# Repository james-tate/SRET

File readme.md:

NOT READY!!!!
Development is in progress. 

An easy to use --open hardware/software-- hardware reverse engineering tool developed using a NXP LPC4330
http://www.nxp.com/products/microcontrollers-and-processors/arm-processors/lpc-mcus/lpc4300-cortex-m4-m0:MC_1403790133078

List of tools that will be implemented:
	flash reader
	jtag
	module interface -- eg(USB->SPI; UART->I2C; etc)
	bus analyzer
	more

NOTES
Do this:
https://launchpad.net/~team-gcc-arm-embedded/+archive/ubuntu/ppa
git submodule init
then make libopencm3
then make

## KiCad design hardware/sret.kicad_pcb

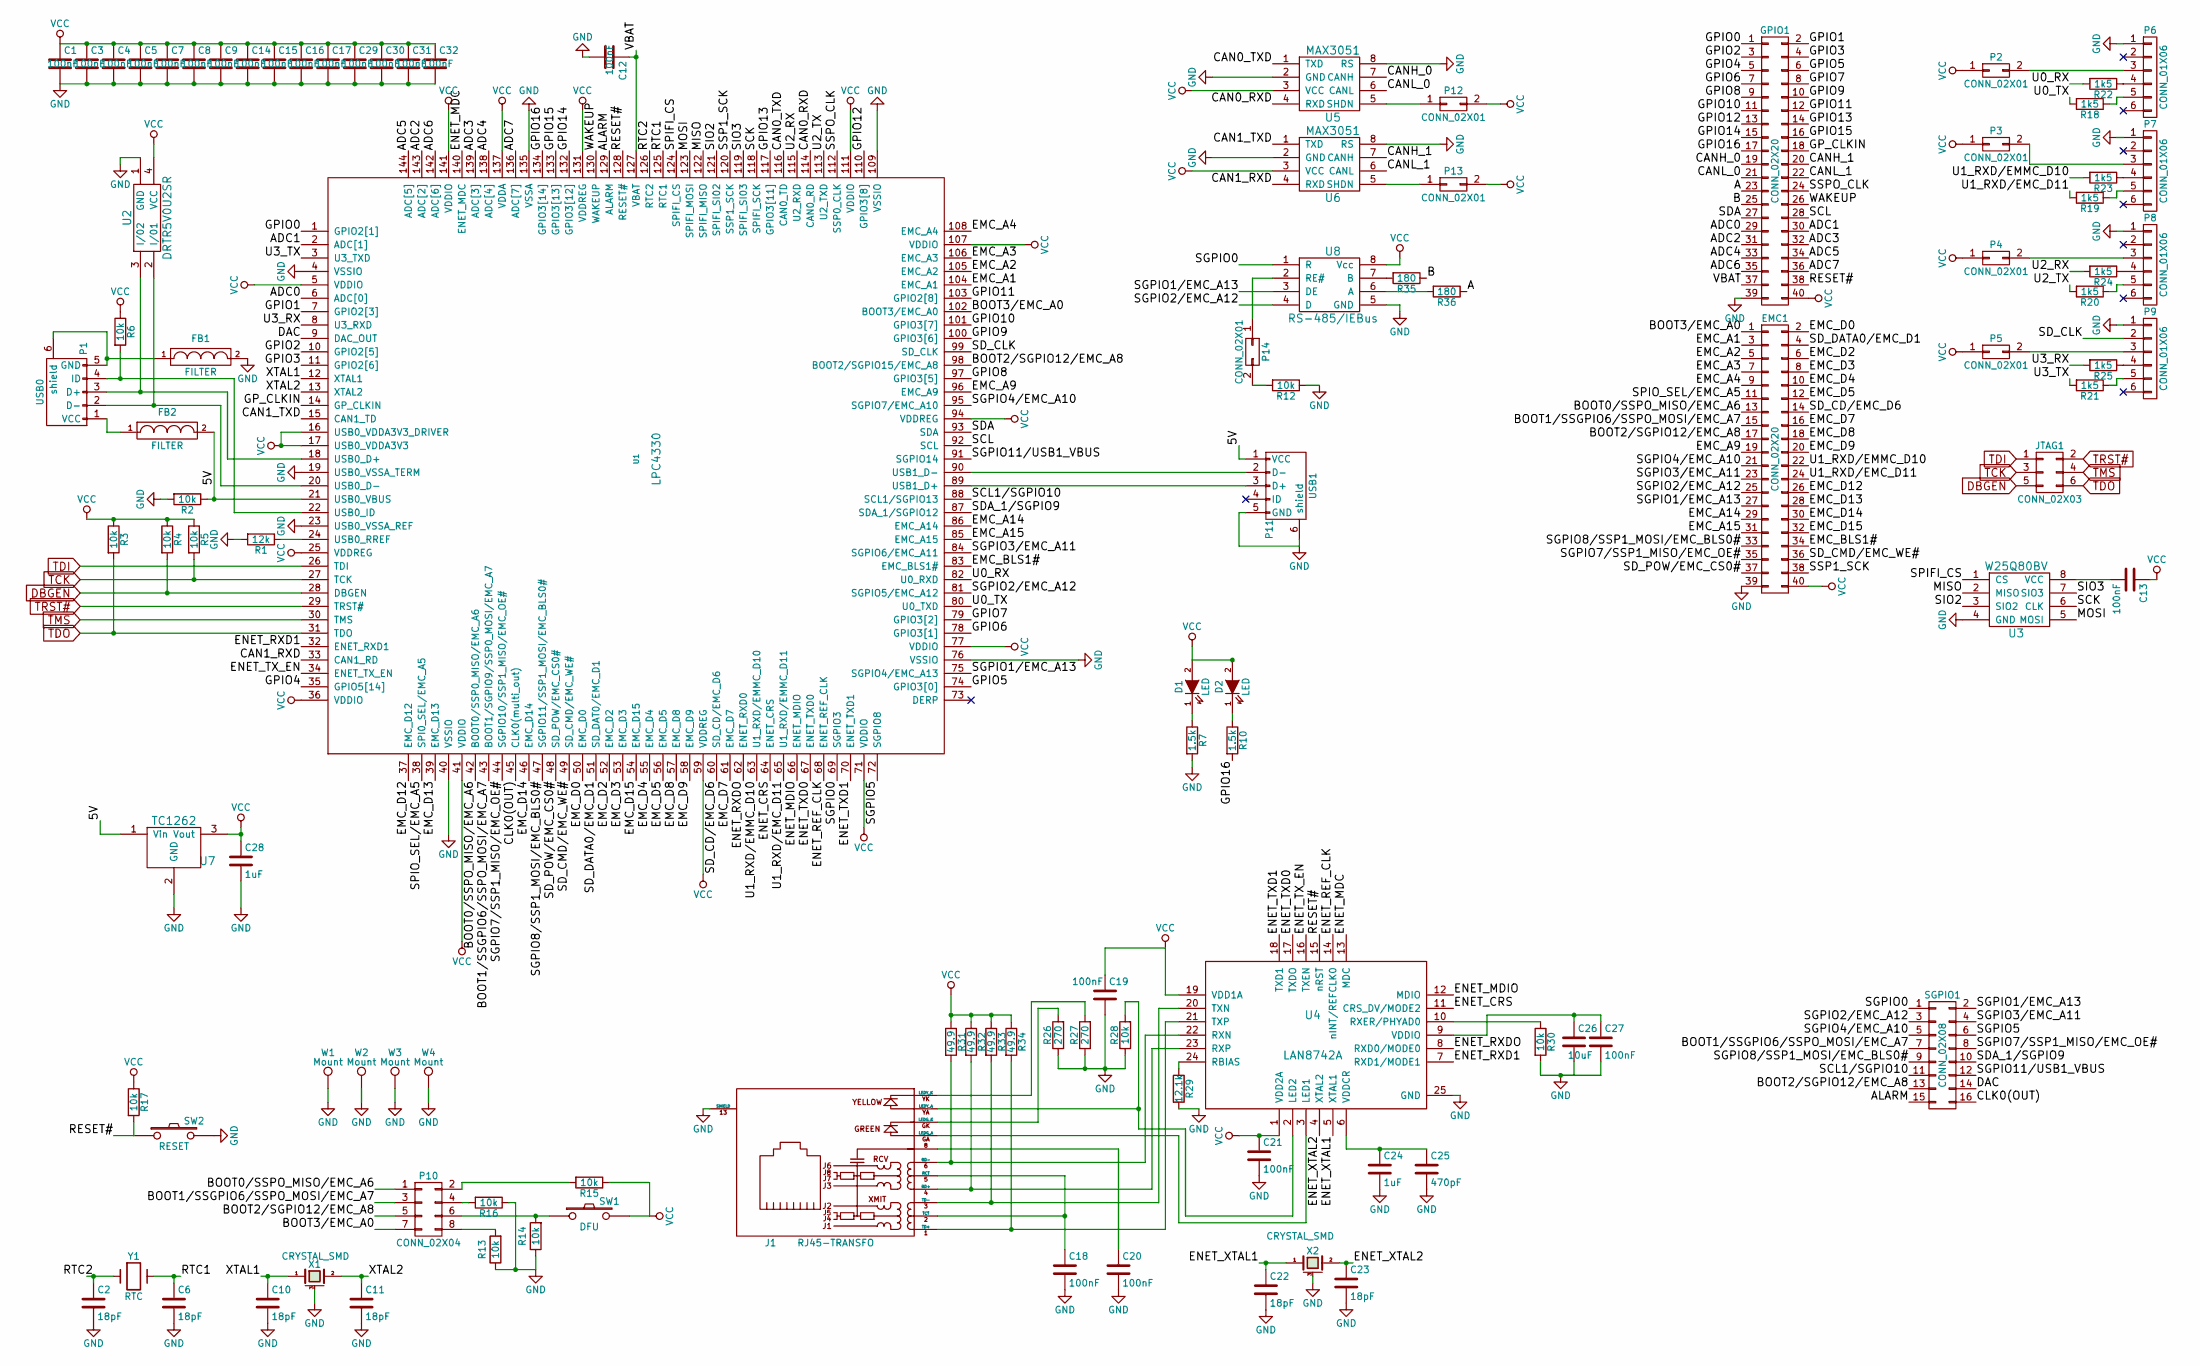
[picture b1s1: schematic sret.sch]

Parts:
C1, C3, C4, C5, C7, C8, C9, C12, C13, C14, C15, C16, C17, C18, C19, C20, C21, C27, C29, C30, C31, C32: 100nF; C_0603
C2, C6, C10, C11, C22, C23: 18pF; C_0603
C24, C28: 1uF; C_0603
C25: 470pF; C_0603
C26: 10uF; C_0603
D1, D2: LED; R_0603_HandSoldering
EMC1: CONN_02X20; Socket_Strip_Straight_2x20
FB1, FB2: FILTER; R_0805_HandSoldering
GPIO1: CONN_02X20; Socket_Strip_Straight_2x20
J1: RJ45-TRANSFO; RJ45_TRANSFO
JTAG1: CONN_02X03; Socket_Strip_Straight_2x03
P1: USB0; USB_Micro-B_circle
P2, P3, P4, P5, P12, P13, P14: CONN_02X01; Pin_Header_Straight_2x01
P6, P7, P8, P9: CONN_01X06; Pin_Header_Straight_1x06
P10: CONN_02X04; Pin_Header_Straight_2x04
P11: USB1; USB_Micro-B_circle
R1: 12k; R_0603
R2, R3, R4, R5, R6, R12, R13, R14, R15, R16, R17, R28, R30: 10k; R_0603
R7, R10: 1.5k; R_0603
R18, R19, R20, R21, R22, R23, R24, R25: 1k5; R_0603
R26, R27: 270; R_0603
R29: 12.1k; R_0603
R31, R32, R33, R34: 49.9; R_0603
R35, R36: 180; R_0603
SGPIO1: CONN_02X08; Socket_Strip_Straight_2x08
SW1: DFU; button
SW2: RESET; button
U1: LPC4330; lqfp144
U2: DRTR5V0U2SR; SOT-143
U3: W25Q80BV; SOIC-8-N
U4: LAN8742A; QFN-24-1EP_4x4mm_Pitch0.5mm
U5, U6: MAX3051; sot-23-8
U7: TC1262; SOT-223
U8: RS-485/IEBus; SOIC-8-N
W1, W2, W3, W4: Mount; MountingHole_2-5mm
X1, X2: CRYSTAL_SMD; crystal_FA238-TSX3225
Y1: RTC; rtc

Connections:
/5V: FB2.2, P11.1 (VCC), R2.1, U1.21 (USB0_VBUS), U7.1 (Vin)
/A: GPIO1.23, R36.1
/ADC0: GPIO1.29, U1.6 (ADC[0])
/ADC1: GPIO1.30, U1.2 (ADC[1])
/ADC2: GPIO1.31, U1.143 (ADC[2])
/ADC3: GPIO1.32, U1.139 (ADC[3])
/ADC4: GPIO1.33, U1.138 (ADC[4])
/ADC5: GPIO1.34, U1.144 (ADC[5])
/ADC6: GPIO1.35, U1.142 (ADC[6])
/ADC7: GPIO1.36, U1.136 (ADC[7])
/ALARM: SGPIO1.15, U1.129 (ALARM)
/B: GPIO1.25, R35.1
/BOOT0/SSPO_MISO/EMC_A6: EMC1.13, P10.1, U1.42 (BOOT0/SSP0_MISO/EMC_A6)
/BOOT1/SSGPIO6/SSPO_MOSI/EMC_A7: EMC1.15, P10.3, SGPIO1.7, U1.43 (BOOT1/SGPIO9/SSP0_MOSI/EMC_A7)
/BOOT2/SGPIO12/EMC_A8: EMC1.17, P10.5, SGPIO1.13, U1.98 (BOOT2/SGPIO15/EMC_A8)
/BOOT3/EMC_A0: EMC1.1, P10.7, U1.102 (BOOT3/EMC_A0)
/CAN0_RXD: U1.114 (CAN0_RD), U5.4 (RXD)
/CAN0_TXD: U1.116 (CAN0_TD), U5.1 (TXD)
/CAN1_RXD: U1.33 (CAN1_RD), U6.4 (RXD)
/CAN1_TXD: U1.15 (CAN1_TD), U6.1 (TXD)
/CANH_0: GPIO1.19, U5.7 (CANH)
/CANH_1: GPIO1.20, U6.7 (CANH)
/CANL_0: GPIO1.21, U5.6 (CANL)
/CANL_1: GPIO1.22, U6.6 (CANL)
/CLK0(OUT): SGPIO1.16, U1.45 (CLK0(multi_out))
/DAC: SGPIO1.14, U1.9 (DAC_OUT)
/EMC_A1: EMC1.3, U1.104 (EMC_A1)
/EMC_A2: EMC1.5, U1.105 (EMC_A2)
/EMC_A3: EMC1.7, U1.106 (EMC_A3)
/EMC_A4: EMC1.9, U1.108 (EMC_A4)
/EMC_A9: EMC1.19, U1.96 (EMC_A9)
/EMC_A14: EMC1.29, U1.86 (EMC_A14)
/EMC_A15: EMC1.31, U1.85 (EMC_A15)
/EMC_BLS1#: EMC1.34, U1.83 (EMC_BLS1#)
/EMC_D0: EMC1.2, U1.50 (EMC_D0)
/EMC_D2: EMC1.6, U1.52 (EMC_D2)
/EMC_D3: EMC1.8, U1.53 (EMC_D3)
/EMC_D4: EMC1.10, U1.55 (EMC_D4)
/EMC_D5: EMC1.12, U1.56 (EMC_D5)
/EMC_D7: EMC1.16, U1.61 (EMC_D7)
/EMC_D8: EMC1.18, U1.57 (EMC_D8)
/EMC_D9: EMC1.20, U1.58 (EMC_D9)
/EMC_D12: EMC1.26, U1.37 (EMC_D12)
/EMC_D13: EMC1.28, U1.39 (EMC_D13)
/EMC_D14: EMC1.30, U1.46 (EMC_D14)
/EMC_D15: EMC1.32, U1.54 (EMC_D15)
/ENET_CRS: U1.64 (ENET_CRS), U4.11 (CRS_DV/MODE2)
/ENET_MDC: U1.140 (ENET_MDC), U4.13 (MDC)
/ENET_MDIO: U1.66 (ENET_MDIO), U4.12 (MDIO)
/ENET_REF_CLK: U1.68 (ENET_REF_CLK), U4.14 (nINT/REFCLK0)
/ENET_RXD1: U1.32 (ENET_RXD1), U4.7 (RXD1/MODE1)
/ENET_RXDO: U1.62 (ENET_RXD0), U4.8 (RXD0/MODE0)
/ENET_TXD0: U1.67 (ENET_TXD0), U4.17 (TXDO)
/ENET_TXD1: U1.70 (ENET_TXD1), U4.18 (TXD1)
/ENET_TX_EN: U1.34 (ENET_TX_EN), U4.16 (TXEN)
/ENET_XTAL1: C22.1, U4.5 (XTAL1), X2.1
/ENET_XTAL2: C23.1, U4.4 (XTAL2), X2.2
/GPIO0: GPIO1.1, U1.1 (GPIO2[1])
/GPIO1: GPIO1.2, U1.7 (GPIO2[3])
/GPIO2: GPIO1.3, U1.10 (GPIO2[5])
/GPIO3: GPIO1.4, U1.11 (GPIO2[6])
/GPIO4: GPIO1.5, U1.35 (GPIO5[14])
/GPIO5: GPIO1.6, U1.74 (GPIO3[0])
/GPIO6: GPIO1.7, U1.78 (GPIO3[1])
/GPIO7: GPIO1.8, U1.79 (GPIO3[2])
/GPIO8: GPIO1.9, U1.97 (GPIO3[5])
/GPIO9: GPIO1.10, U1.100 (GPIO3[6])
/GPIO10: GPIO1.11, U1.101 (GPIO3[7])
/GPIO11: GPIO1.12, U1.103 (GPIO2[8])
/GPIO12: GPIO1.13, U1.110 (GPIO3[8])
/GPIO13: GPIO1.14, U1.117 (GPIO3[11])
/GPIO14: GPIO1.15, U1.132 (GPIO3[12])
/GPIO15: GPIO1.16, U1.133 (GPIO3[13])
/GPIO16: GPIO1.17, R10.2, U1.134 (GPIO3[14])
/GP_CLKIN: GPIO1.18, U1.14 (GP_CLKIN)
/MISO: U1.122 (SPIFI_MISO), U3.2 (MISO)
/MOSI: U1.123 (SPIFI_MOSI), U3.5 (MOSI)
/RESET#: GPIO1.38, R17.2, SW2.1, U1.128 (RESET#), U4.15 (nRST)
/RTC1: C6.1, U1.125 (RTC1), Y1.2
/RTC2: C2.1, U1.126 (RTC2), Y1.1
/SCK: U1.118 (SPIFI_SCK), U3.6 (CLK)
/SCL: GPIO1.28, U1.92 (SCL)
/SCL1/SGPIO10: SGPIO1.11, U1.88 (SCL1/SGPIO13)
/SDA: GPIO1.27, U1.93 (SDA)
/SDA_1/SGPIO9: SGPIO1.10, U1.87 (SDA_1/SGPIO12)
/SD_CD/EMC_D6: EMC1.14, U1.60 (SD_CD/EMC_D6)
/SD_CLK: P9.2, U1.99 (SD_CLK)
/SD_CMD/EMC_WE#: EMC1.36, U1.49 (SD_CMD/EMC_WE#)
/SD_DATA0/EMC_D1: EMC1.4, U1.51 (SD_DAT0/EMC_D1)
/SD_POW/EMC_CS0#: EMC1.37, U1.48 (SD_POW/EMC_CS0#)
/SGPIO0: SGPIO1.1, U1.69 (SGPIO3), U8.1 (R)
/SGPIO1/EMC_A13: EMC1.27, SGPIO1.2, U1.75 (SGPIO4/EMC_A13), U8.3 (DE)
/SGPIO2/EMC_A12: EMC1.25, SGPIO1.3, U1.81 (SGPIO5/EMC_A12), U8.4 (D)
/SGPIO3/EMC_A11: EMC1.23, SGPIO1.4, U1.84 (SGPIO6/EMC_A11)
/SGPIO4/EMC_A10: EMC1.21, SGPIO1.5, U1.95 (SGPIO7/EMC_A10)
/SGPIO5: SGPIO1.6, U1.72 (SGPIO8)
/SGPIO7/SSP1_MISO/EMC_OE#: EMC1.35, SGPIO1.8, U1.44 (SGPIO10/SSP1_MISO/EMC_OE#)
/SGPIO8/SSP1_MOSI/EMC_BLS0#: EMC1.33, SGPIO1.9, U1.47 (SGPIO11/SSP1_MOSI/EMC_BLS0#)
/SGPIO11/USB1_VBUS: SGPIO1.12, U1.91 (SGPIO14)
/SIO2: U1.121 (SPIFI_SI02), U3.3 (SIO2)
/SIO3: U1.119 (SPIFI_SI03), U3.7 (SIO3)
/SPIFI_CS: U1.124 (SPIFI_CS), U3.1 (CS)
/SPIO_SEL/EMC_A5: EMC1.11, U1.38 (SPI0_SEL/EMC_A5)
/SSP1_SCK: EMC1.38, U1.120 (SSP1_SCK)
/SSPO_CLK: GPIO1.24, U1.112 (SSP0_CLK)
/U0_RX: R22.2, U1.82 (U0_RXD)
/U0_TX: R18.2, U1.80 (U0_TXD)
/U1_RXD/EMC_D11: EMC1.24, R19.2, U1.65 (U1_RXD/EMMC_D11)
/U1_RXD/EMMC_D10: EMC1.22, R23.2, U1.63 (U1_RXD/EMMC_D10)
/U2_RX: R24.2, U1.115 (U2_RXD)
/U2_TX: R20.2, U1.113 (U2_TXD)
/U3_RX: R25.2, U1.8 (U3_RXD)
/U3_TX: R21.2, U1.3 (U3_TXD)
/VBAT: C12.1, GPIO1.37, U1.127 (VBAT)
/WAKEUP: GPIO1.26, U1.130 (WAKEUP)
/XTAL1: C10.1, U1.12 (XTAL1), X1.1
/XTAL2: C11.1, U1.13 (XTAL2), X1.2
DBGEN: JTAG1.5, R4.2, U1.28 (DBGEN)
GND: C1.2, C2.2, C3.2, C4.2, C5.2, C6.2, C7.2, C8.2, C9.2, C10.2, C11.2, C12.2, C14.2, C15.2, C16.2, C17.2, C18.2, C19.2, C20.2, C21.2, C22.2, C23.2, C24.2, C25.2, C26.2, C27.2, C28.2, C29.2, C30.2, C31.2, C32.2, EMC1.39, FB1.2, GPIO1.39, J1.13 (SHIELD), P6.1, P7.1, P8.1, P9.1, P11.5 (GND), P11.6 (shield), R1.2, R2.2, R7.2, R12.1, R13.1, R14.1, R16.1, R26.1, R27.1, R28.1, R29.2, R30.2, SW2.2, U1.4 (VSSIO), U1.19 (USB0_VSSA_TERM), U1.23 (USB0_VSSA_REF), U1.40 (VSSIO), U1.76 (VSSIO), U1.109 (VSSIO), U1.135 (VSSA), U2.1 (GND), U3.4 (GND), U4.25 (GND), U5.2 (GND), U5.8 (RS), U6.2 (GND), U6.8 (RS), U7.2 (GND), U8.5 (GND), W1.1, W2.1, W3.1, W4.1, X1.3 (case), X2.3 (case)
unnamed: C13.2, U3.8 (VCC)
unnamed: C18.1, J1.2 (TCT), J1.5 (RCT)
unnamed: C20.1, J1.8
unnamed: C24.1, C25.1, U4.6 (VDDCR)
unnamed: C26.1, C27.1, U4.9 (VDDIO)
unnamed: D1.1 (K), R7.1
unnamed: D2.1 (K), R10.1
unnamed: FB1.1, P1.5 (GND), P1.6 (shield)
unnamed: FB2.1, P1.1 (VCC)
unnamed: J1.1 (TD+), R34.2, U4.21 (TXP)
unnamed: J1.3 (TD-), R33.2, U4.20 (TXN)
unnamed: J1.4 (RD+), R32.2, U4.23 (RXP)
unnamed: J1.6 (RD-), R31.2, U4.22 (RXN)
unnamed: J1.GA (LEDG_A), U4.3 (LED1)
unnamed: J1.GK (LEDG_K), R26.2
unnamed: J1.YA (LEDY_A), R28.2, U4.2 (LED2)
unnamed: J1.YK (LEDY_K), R27.2
unnamed: P1.2 (D-), U1.20 (USB0_D-), U2.2 (I/01)
unnamed: P1.3 (D+), U1.18 (USB0_D+), U2.3 (I/02)
unnamed: P1.4 (ID), R6.2, U1.22 (USB0_ID)
unnamed: P2.2, P6.3
unnamed: P3.2, P7.3
unnamed: P4.2, P8.3
unnamed: P5.2, P9.3
unnamed: P6.4, R22.1
unnamed: P6.5, R18.1
unnamed: P7.4, R23.1
unnamed: P7.5, R19.1
unnamed: P8.4, R24.1
unnamed: P8.5, R20.1
unnamed: P9.4, R25.1
unnamed: P9.5, R21.1
unnamed: P10.2, R15.2
unnamed: P10.4, R16.2
unnamed: P10.6, R14.2, SW1.1
unnamed: P10.8, R13.2
unnamed: P11.2 (D-), U1.90 (USB1_D-)
unnamed: P11.3 (D+), U1.89 (USB1_D+)
unnamed: P12.1, U5.5 (SHDN)
unnamed: P13.1, U6.5 (SHDN)
unnamed: P14.1, U8.2 (RE#)
unnamed: P14.2, R12.2
unnamed: R1.1, U1.24 (USB0_RREF)
unnamed: R29.1, U4.24 (RBIAS)
unnamed: R30.1, U4.10 (RXER/PHYAD0)
unnamed: R35.2, U8.7 (B)
unnamed: R36.2, U8.6 (A)
TCK: JTAG1.3, R5.2, U1.27 (TCK)
TDI: JTAG1.1, U1.26 (TDI)
TDO: JTAG1.6, R3.2, U1.31 (TDO)
TMS: JTAG1.4, U1.30 (TMS)
TRST#: JTAG1.2, U1.29 (TRST#)
VCC: C1.1, C3.1, C4.1, C5.1, C7.1, C8.1, C9.1, C13.1, C14.1, C15.1, C16.1, C17.1, C19.1, C21.1, C28.1, C29.1, C30.1, C31.1, C32.1, D1.2 (A), D2.2 (A), EMC1.40, GPIO1.40, P2.1, P3.1, P4.1, P5.1, P12.2, P13.2, R3.1, R4.1, R5.1, R6.1, R15.1, R17.1, R31.1, R32.1, R33.1, R34.1, SW1.2, U1.5 (VDDIO), U1.16 (USB0_VDDA3V3_DRIVER), U1.17 (USB0_VDDA3V3), U1.25 (VDDREG), U1.36 (VDDIO), U1.41 (VDDIO), U1.59 (VDDREG), U1.71 (VDDIO), U1.77 (VDDIO), U1.94 (VDDREG), U1.107 (VDDIO), U1.111 (VDDIO), U1.131 (VDDREG), U1.137 (VDDA), U1.141 (VDDIO), U2.4 (VCC), U4.1 (VDD2A), U4.19 (VDD1A), U5.3 (VCC), U6.3 (VCC), U7.3 (Vout), U8.8 (Vcc)

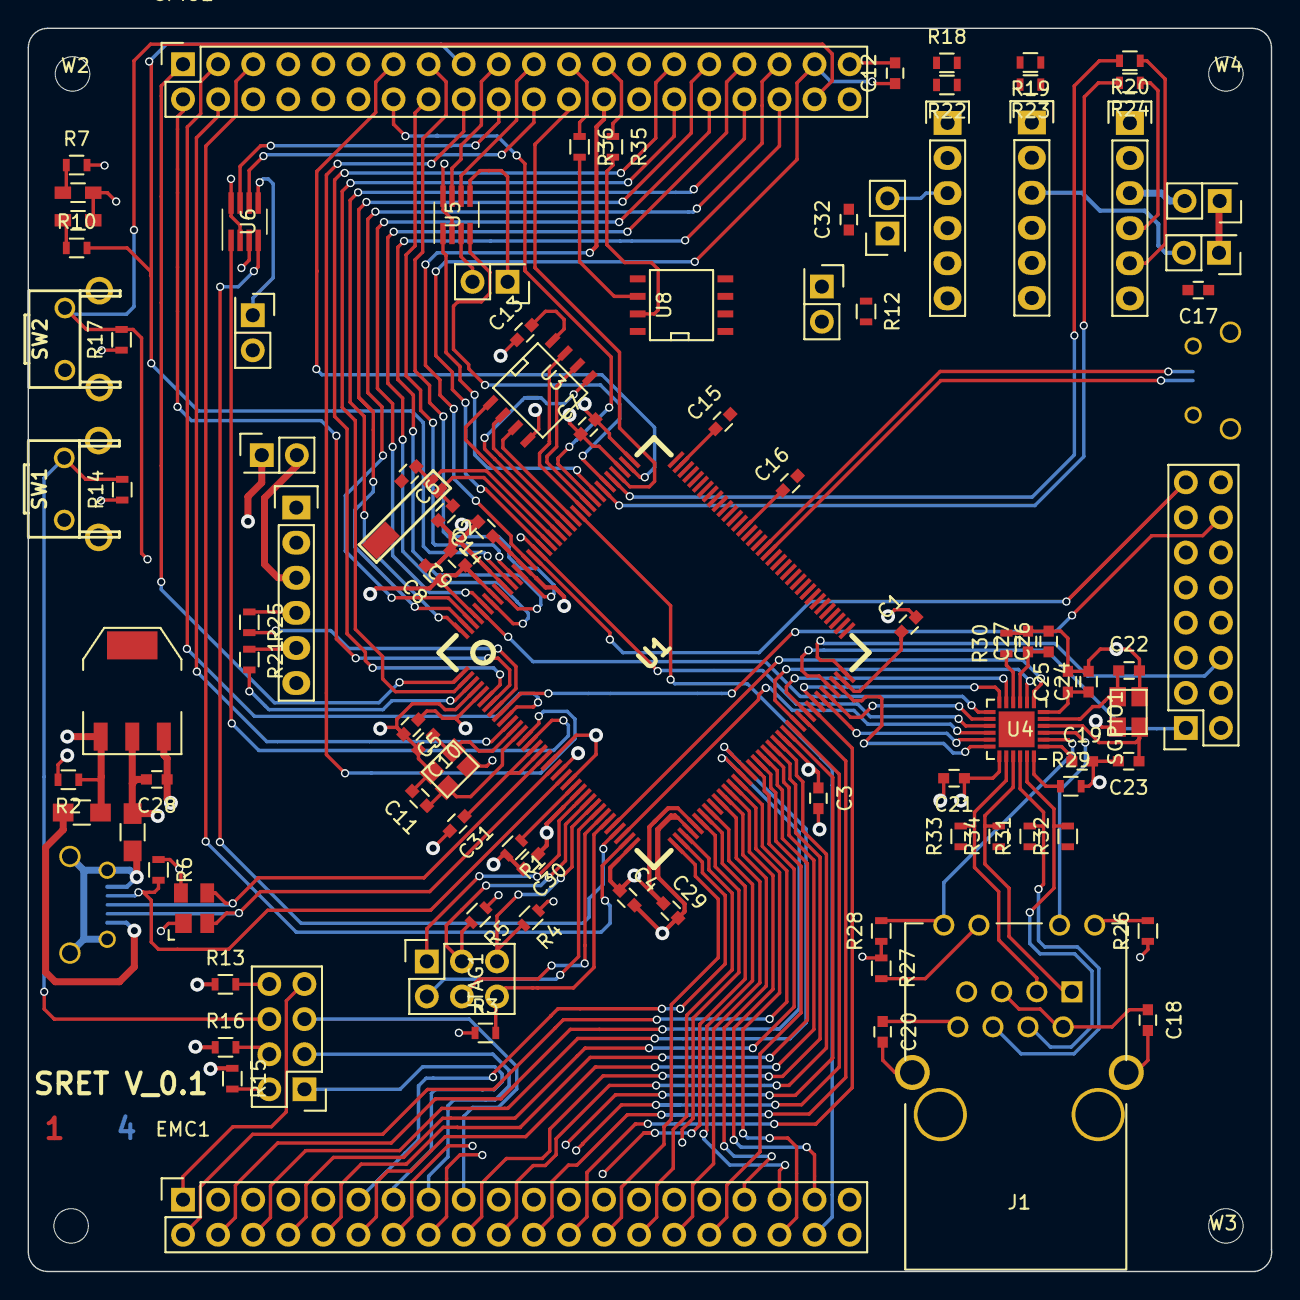
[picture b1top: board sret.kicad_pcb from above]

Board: 4 copper layers, 90.0 x 90.0 mm, 105 parts (0 on the bottom side), 172 nets.

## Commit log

2017-02-21 added libopencm3 submodule, early readme
2017-03-05 kicad project
2017-03-05 added kicad ignore
2017-03-07 started kicad lib
2017-03-07 need .lib files for kicad
2017-03-07 added kicad lib
2017-03-07 update lib
2017-03-08 lpc lib update
2017-03-10 port mappings
2017-03-12 pin mapping done
2017-03-13 sch update
2017-03-15 alpha alpha schematic
2017-03-15 update gitignore
2017-03-17 lpc4330 footprint
2017-03-17 almost finised with footprint
2017-03-20 footprint finished, starting PCB
2017-03-21 rough pcb layout
2017-03-21 readme wrong ext
2017-03-26 added RS485/IEBus chip
2017-03-26 update back photo
2017-03-27 pcb routing started
2017-03-27 saving before fix permissions
2017-03-28 working on traces
2017-03-29 2nd version pcb
2017-04-01 update pcb
2017-04-01 pcb edges
2017-04-03 more traces
